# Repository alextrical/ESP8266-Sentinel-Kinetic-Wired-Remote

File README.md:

# ESP8266-Vent-Axia-Sentinel-Kinetic-Wired-Remote-Controller
ESP8266 based Re-implementation of the Vent-Axia Sentinel Kinetic Wired Remote Controller
Firmware to be checked over once the PCB is manufactured, but Arduino sketch can be simulated here
https://wokwi.com/projects/427157112827024385

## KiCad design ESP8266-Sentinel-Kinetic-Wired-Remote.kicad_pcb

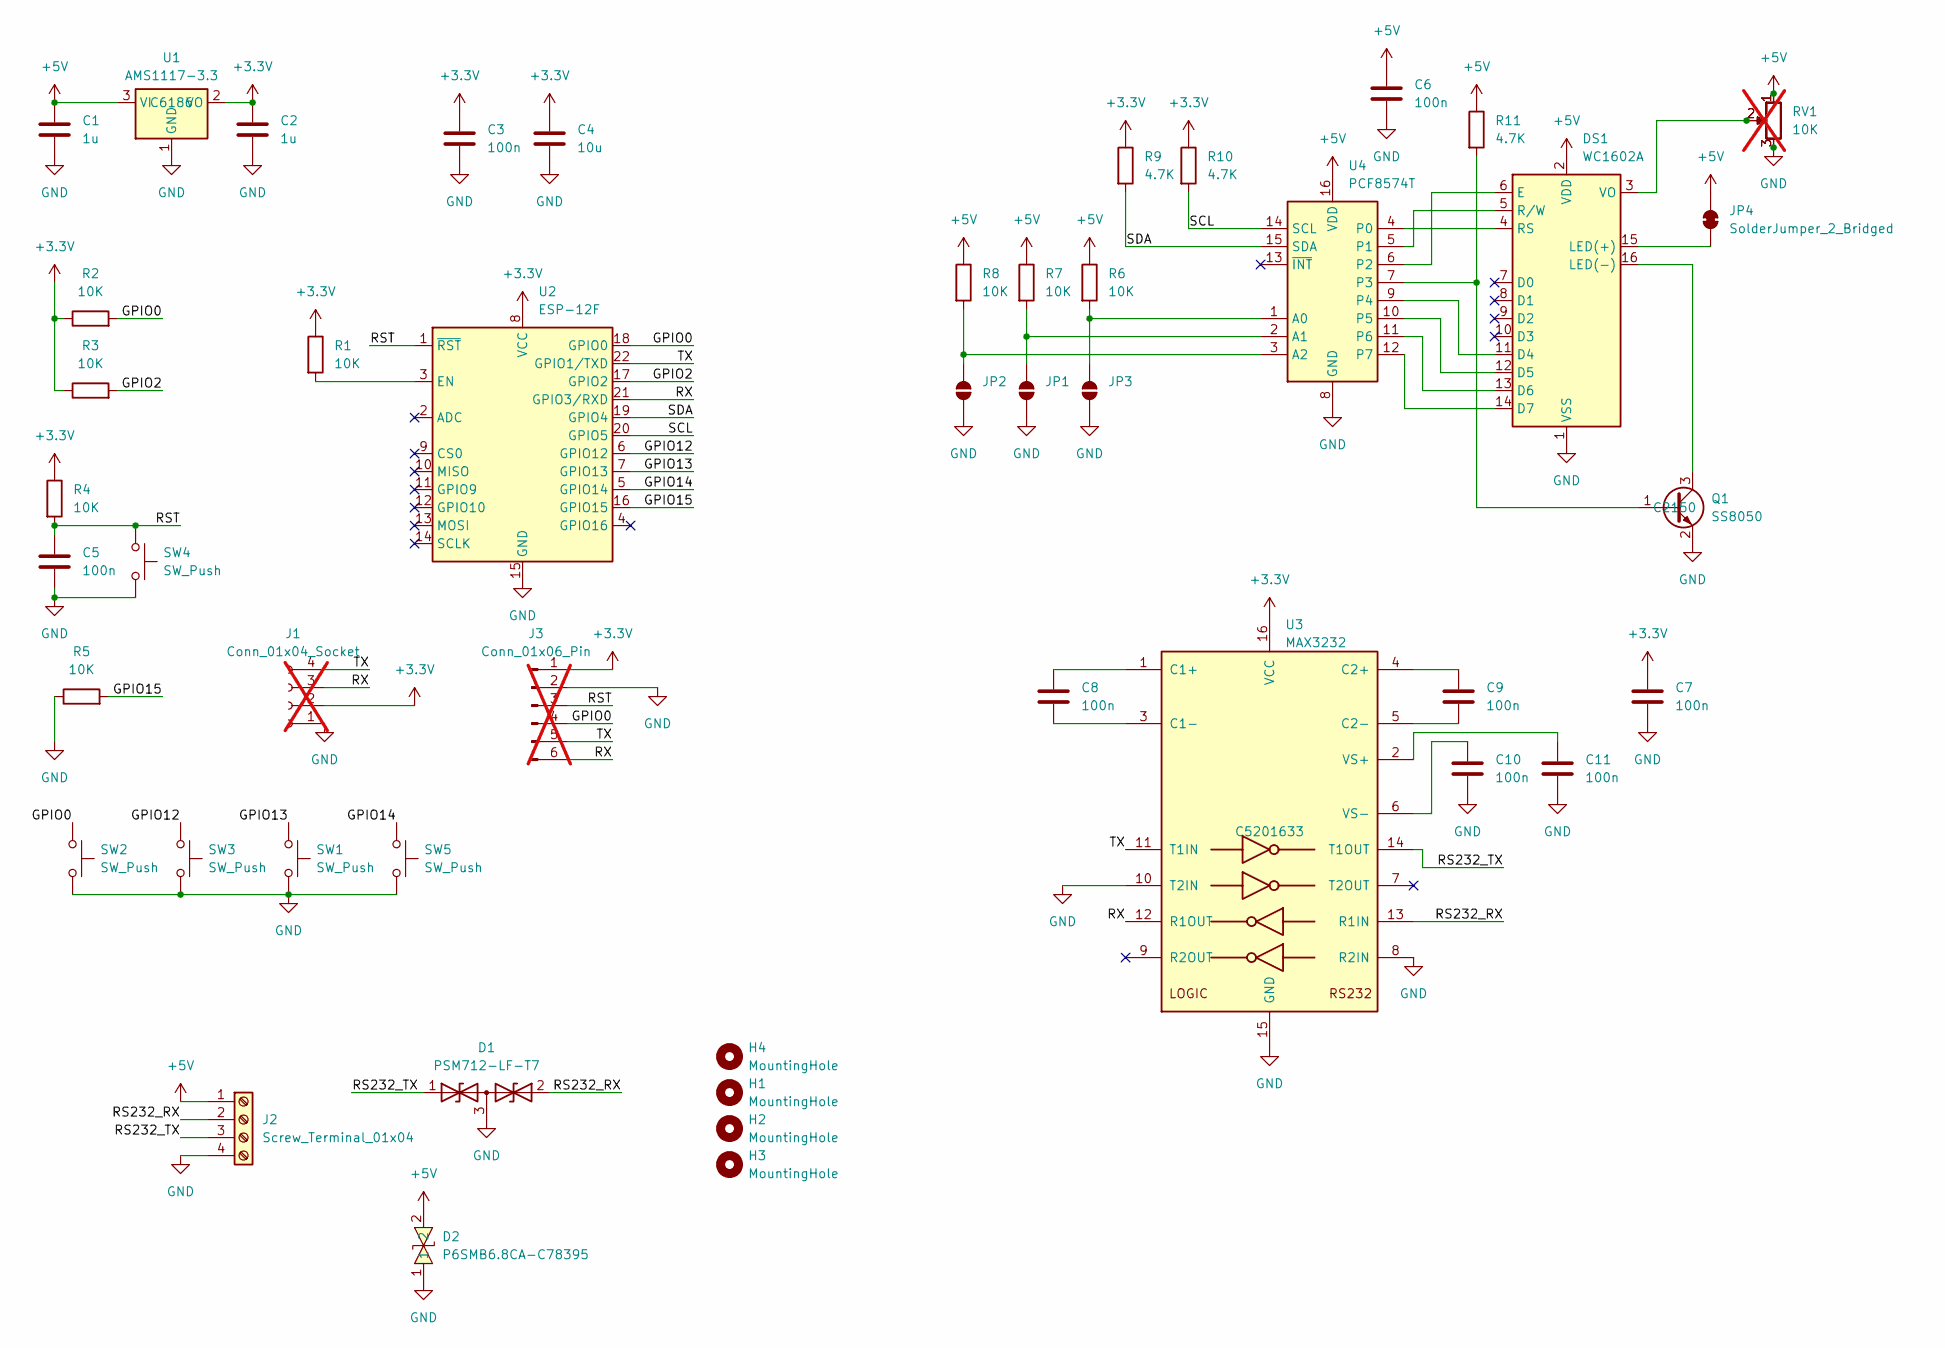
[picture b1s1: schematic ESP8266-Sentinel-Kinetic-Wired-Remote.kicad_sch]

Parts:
C1, C2: 1u; C_0402_1005Metric; LCSC C52923
C3, C5, C6, C7, C8, C9, C10, C11: 100n; C_0402_1005Metric; LCSC C307331
C4: 10u; C_0402_1005Metric; LCSC C15525
D1: PSM712-LF-T7; SOT-23; LCSC C32677
D2: P6SMB6.8CA-C78395; SMB_L4.6-W3.6-LS5.3-BI; LCSC Part C78395
DS1: WC1602A
H1, H2, H3, H4: MountingHole; MountingHole_3.2mm_M3
J1: Conn_01x04_Socket; PinSocket_1x04_P2.54mm_Vertical; not fitted
J2: Screw_Terminal_01x04; TerminalBlock_4Ucon_1x04_P3.50mm_Horizontal
J3: Conn_01x06_Pin; PinSocket_1x06_P1.27mm_Vertical; not fitted
JP1, JP2, JP3: SolderJumper_2_Open; SolderJumper-2_P1.3mm_Open_RoundedPad1.0x1.5mm
JP4: SolderJumper_2_Bridged; SolderJumper-2_P1.3mm_Bridged2Bar_RoundedPad1.0x1.5mm
Q1: SS8050; SOT-23; LCSC C2150
R1, R2, R3, R4, R5, R6, R7, R8: 10K; R_0402_1005Metric; LCSC C25744
R9, R10, R11: 4.7K; R_0402_1005Metric; LCSC C25900
RV1: 10K; Potentiometer_Runtron_RM-065_Vertical
RV2: 10K; Potentiometer_ACP_CA14V-15_Vertical; not fitted
SW1, SW2, SW3, SW4, SW5: SW_Push; SW_PUSH_6mm
U1: AMS1117-3.3; SOT-223-3_TabPin2; LCSC C6186
U2: ESP-12F; ESP-12E
U3: MAX3232; SOP-16_3.9x9.9mm_P1.27mm; LCSC C5201633
U4: PCF8574T; SOIC-16_3.9x9.9mm_P1.27mm; LCSC C5310792

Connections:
+3.3V: C2.1, C3.1, C4.1, C7.1, J1.2, J3.1, R1.1, R2.1, R3.1, R4.1, R9.1, R10.1, U1.2 (VO), U2.8 (VCC), U3.16 (VCC)
+5V: C1.1, C6.1, D2.2, DS1.2 (VDD), J2.1, JP4.2 (B), R6.1, R7.1, R8.1, R11.1, RV1.1, RV2.1, U1.3 (VI), U4.16 (VDD)
/GPIO0: J3.4, R2.2, SW2.1, U2.18 (GPIO0)
/GPIO2: R3.2, U2.17 (GPIO2)
/GPIO12: SW3.1, U2.6 (GPIO12)
/GPIO13: SW1.1, U2.7 (GPIO13)
/GPIO14: SW5.1, U2.5 (GPIO14)
/GPIO15: R5.2, U2.16 (GPIO15)
/RS232_RX: D1.2 (A2), J2.2, U3.13 (R1IN)
/RS232_TX: D1.1 (A1), J2.3, U3.14 (T1OUT)
/RST: C5.1, J3.3, R4.2, SW4.1, U2.1 (~RST)
/RX: J1.3, J3.6, U2.21 (GPIO3/RXD), U3.12 (R1OUT)
/SCL: R10.2, U2.20 (GPIO5), U4.14 (SCL)
/SDA: R9.2, U2.19 (GPIO4), U4.15 (SDA)
/TX: J1.4, J3.5, U2.22 (GPIO1/TXD), U3.11 (T1IN)
GND: C1.2, C2.2, C3.2, C4.2, C5.2, C6.2, C7.2, C10.2, C11.2, D1.3 (common), D2.1, DS1.1 (VSS), J1.1, J2.4, J3.2, JP1.1 (A), JP2.1 (A), JP3.1 (A), Q1.2 (E), R5.1, RV1.3, RV2.3, SW1.2, SW2.2, SW3.2, SW4.2, SW5.2, U1.1 (GND), U2.15 (GND), U3.8 (R2IN), U3.10 (T2IN), U3.15 (GND), U4.8 (GND)
unnamed: DS1.11 (D4), U4.9 (P4)
unnamed: DS1.12 (D5), U4.10 (P5)
unnamed: DS1.13 (D6), U4.11 (P6)
unnamed: DS1.14 (D7), U4.12 (P7)
unnamed: DS1.6 (E), U4.6 (P2)
unnamed: DS1.15 (LED(+)), JP4.1 (A)
unnamed: DS1.16 (LED(-)), Q1.3 (C)
unnamed: DS1.4 (RS), U4.4 (P0)
unnamed: DS1.5 (R/W), U4.5 (P1)
unnamed: DS1.3 (VO), RV1.2, RV2.2
unnamed: JP1.2 (B), R7.2, U4.2 (A1)
unnamed: JP2.2 (B), R8.2, U4.3 (A2)
unnamed: JP3.2 (B), R6.2, U4.1 (A0)
unnamed: Q1.1 (B), R11.2, U4.7 (P3)
unnamed: R1.2, U2.3 (EN)
unnamed: C8.1, U3.1 (C1+)
unnamed: C8.2, U3.3 (C1-)
unnamed: C9.1, U3.4 (C2+)
unnamed: C9.2, U3.5 (C2-)
unnamed: C11.1, U3.2 (VS+)
unnamed: C10.1, U3.6 (VS-)

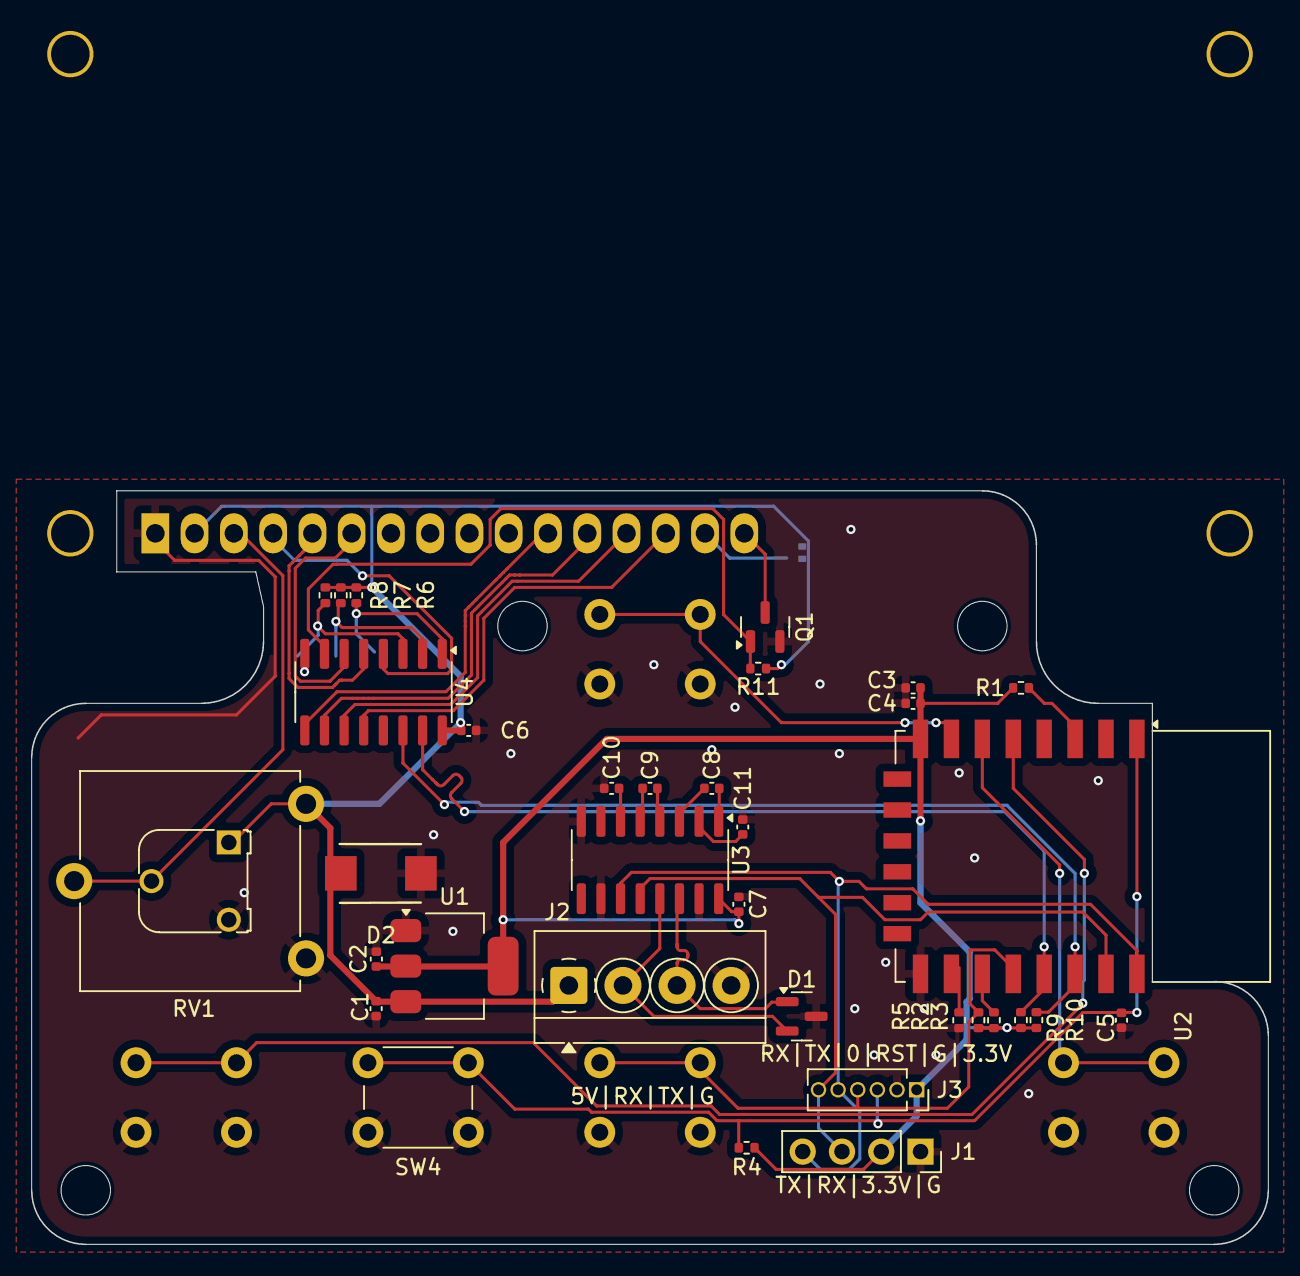
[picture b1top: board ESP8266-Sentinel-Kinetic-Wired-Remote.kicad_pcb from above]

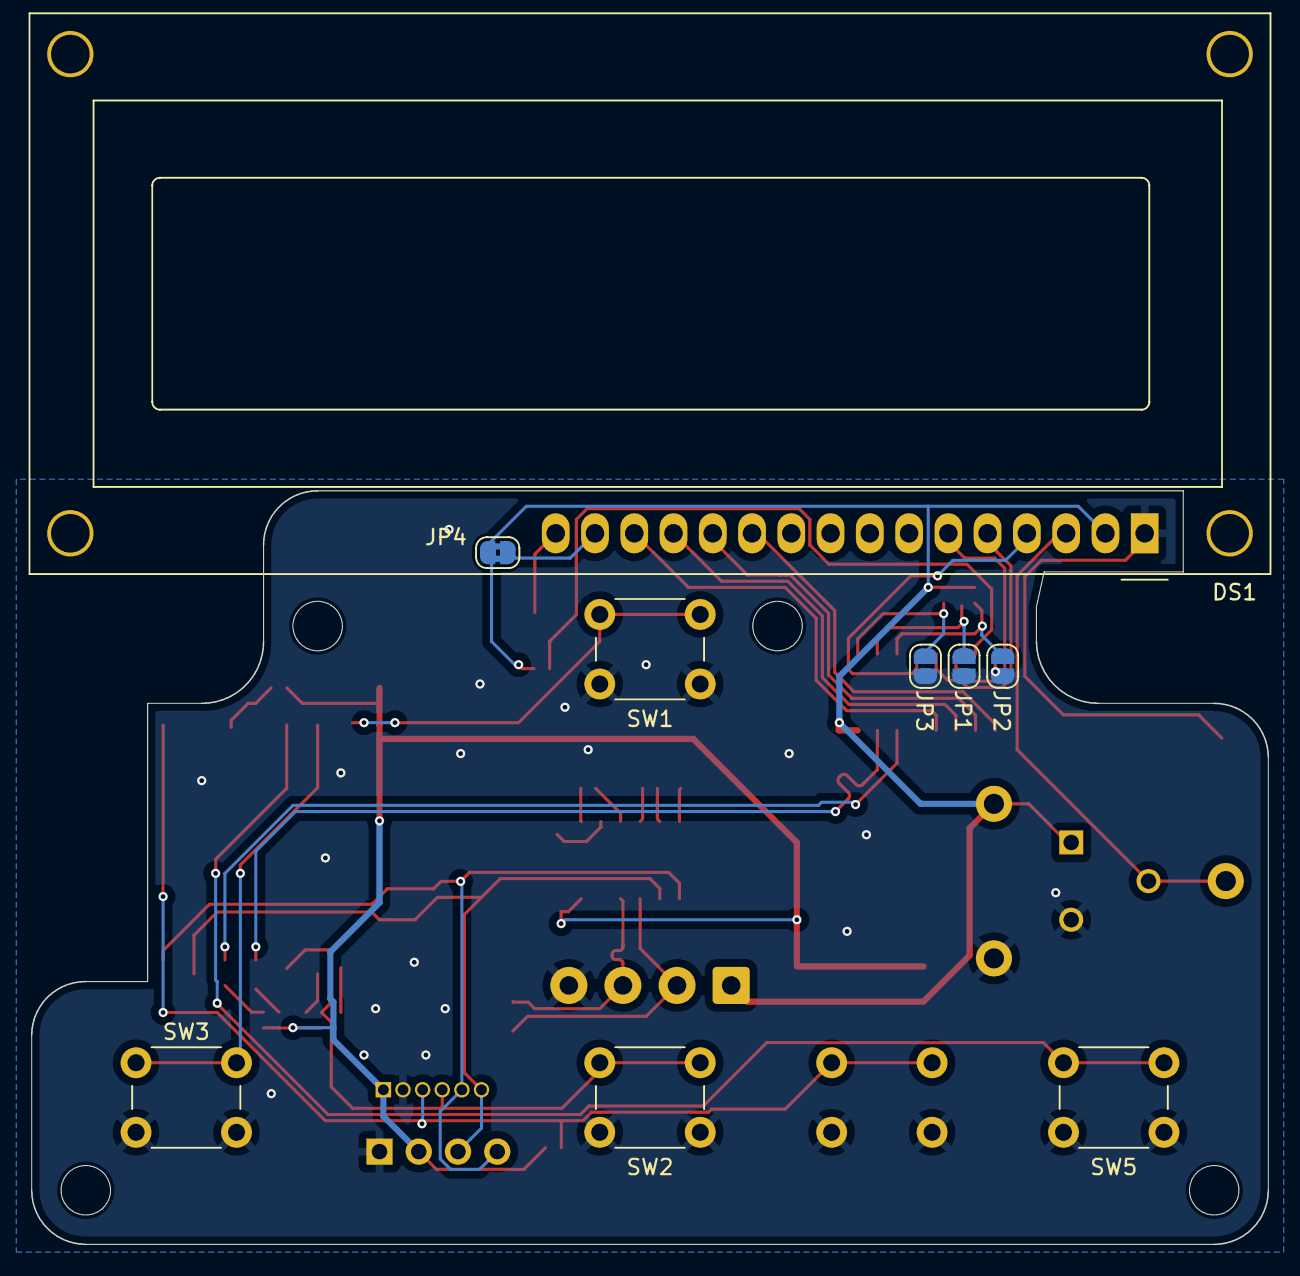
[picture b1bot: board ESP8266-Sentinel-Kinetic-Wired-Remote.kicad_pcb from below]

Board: 2 copper layers, 80.0 x 48.8 mm, 48 parts (9 on the bottom side), 37 nets.

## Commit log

2025-04-04 Initial schematic
2025-04-12 Layed out PCB and created 3D printable enclosure
2025-04-13 Added JLCPCB part numbers Rotated programming ports
2025-04-13 Change Workflows to remove missing submodule
2025-04-13 Add JLCPCB part number for SS8050 Remove panel creation action
2025-04-13 Replaced PCF8574 package
2025-04-13 Added TVS diodes for protection
2025-04-22 Add Arduino based source code
2025-05-14 Upload schematic
